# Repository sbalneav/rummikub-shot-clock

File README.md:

# Rummikub Shot Clock

A 60-second turn timer that fits inside one of those novelty "Easy" buttons. Press the button to end your turn: the next player's 60 seconds start. If time runs out, it beeps until somebody presses the button.

- **Project home:** https://github.com/sbalneav/rummikub-shot-clock
- **Illustrated overview:** https://claude.ai/artifact/5sadpqRUegUsPd4Guqu1sk (schematic, how it works and parts, in a page that's easy to read on a phone)

> **Status: rev A, not yet built or tested.** The schematic and PCB pass KiCad's design-rule check, but nobody has built a board yet. Breadboard it first, and please open an issue with what you find.

## How it works

| Stage | Part | What it does |
|---|---|---|
| Timer | U1 (555) | A one-shot. The Easy Button shorts the timing cap C1, which triggers the 555 and restarts the count. After about 1.1 × (R1 + VR1) × C1, the output goes low. Pin 7 is not used, so C1 keeps charging and the timer never retriggers itself. |
| Inverter | Q1 | Turns "timer finished" into ALARM high. |
| Tone | U2 (555) | An oscillator at about 1.5 kHz, held in reset until ALARM goes high. |
| Pulser (optional) | U3 (555) | About 2 Hz on/off, for a beep-beep-beep instead of a steady tone. Set it with JP1. |
| Driver | Q2 | Drives the button's 8 Ω speaker. |

What it does when used:

- **Every press restarts the full time**, whether you press during the countdown or during the beep. Contact bounce doesn't matter.
- **At power-on the countdown starts by itself.**

The optional pulser is shown here:

## Choosing a 555 and a battery

The board takes either type of 555. They have the same pinout and footprint, so the only difference is the power supply.

| Chips | Battery | R9 | Idle current | Notes |
|---|---|---|---|---|
| **TLC555 / LMC555 / ICM7555** (CMOS) | 2×AA or 2×AAA (3 V) | 10 Ω ¼ W | ~0.3 mA | Lowest drain. Uses the button's own 2-cell holder if it has one |
| **NE555** (bipolar) | 4×AA or 4×AAA (6 V) | 22 Ω ½ W | ~10–15 mA | The cheap 555s from bulk packs |
| **NE555** (bipolar) | 9 V battery | 47 Ω ½ W | ~10–15 mA | Fewer hours, but easy to fit |

- **An NE555 needs at least 4.5 V,** so it won't run from 2 cells. 3 cells (4.5 V) is marginal and quits as the batteries run down. Use 4 cells or a 9 V battery.
- **R9 sets the speaker current.** Raise it with the supply voltage as shown so it doesn't overheat.
- **Nothing else changes.** The turn length works the same at any supply voltage, so VR1 has the same range. The capacitors are rated 16 V.
- **Current while beeping** is about 150–200 mA with any option. Use the power switch between game nights, especially with NE555s.

## Ordering boards

Upload **`pcb/rummikub-shot-clock-gerbers.zip`** to any PCB fab (JLCPCB, PCBWay, OSH Park and so on).

| Setting | Value |
|---|---|
| Layers | 2 |
| Size | 72 × 58 mm |
| Thickness | 1.6 mm |
| Copper | 1 oz |
| Minimum track / space | 0.4 / 0.25 mm |
| Smallest drill | 0.45 mm (vias) |
| Parts | All through-hole |

The default settings at any fab will do.

| Front | Back |
|---|---|
|  |  |

**Check the size before you order.** Measure the inside of your Easy Button. The board is 72 × 58 mm and has two M3 mounting holes. If it doesn't fit, the layout scripts in `tools/` make it easy to change the outline and rebuild.

## Parts

See [`pcb/BOM.csv`](pcb/BOM.csv). For a steady tone only, leave out U3, R10, R11, C5, C7 and C10, and fit the JP1 jumper on pins 1-2.

## Building and setup

1. **Gut the button.** Cut or lift the traces from the original sound chip to the dome switch and the speaker. Wire those to J3 (BUTTON) and J4 (SPKR). Wire the battery to J1 and an on/off switch to J2. Choose the battery and R9 from the table under "Choosing a 555 and a battery".
2. **Check transistor pinouts.** The footprints are E-B-C, which matches the 2N3904, PN2222A and 2N4401. Some parts sold as 2N2222 are C-B-E.
3. **Set the time.** Use a stopwatch and adjust VR1 until the beep comes at 60 s, timing from when you release the button. Electrolytic caps vary by ±20%, so the formula only gets you close. Check again after a few hours powered, because new caps drift.
4. **Choose steady or pulsed.** JP1 on 1-2 gives a steady tone. On 2-3 it gives a pulsed beep.

## Repository layout

```
schematic/   schematic as PNG, SVG and PDF, plus the pulser add-on
pcb/         KiCad 9 board, Gerbers + drill (zipped), BOM, renders, DRC report
tools/       the Python scripts that generated the schematic and the board
```

The board was generated by script with the KiCad 9 `pcbnew` Python API and autorouted with [Freerouting](https://github.com/freerouting/freerouting). To rebuild it, run `tools/build_board.py`, export Specctra DSN, route it with Freerouting, then run `tools/finish_board.py`. You can also open `pcb/rummikub-shot-clock.kicad_pcb` in KiCad and edit it by hand. The DRC report lists one harmless warning: a small fragment of ground fill near C4, whose ground pin has its own trace.

## Credits and license

Designed by Scott Balneaves with Claude (Anthropic's AI model), which did the circuit design, schematic and PCB layout.

Hardware is licensed under the [CERN Open Hardware Licence v2 – Permissive](LICENSE).

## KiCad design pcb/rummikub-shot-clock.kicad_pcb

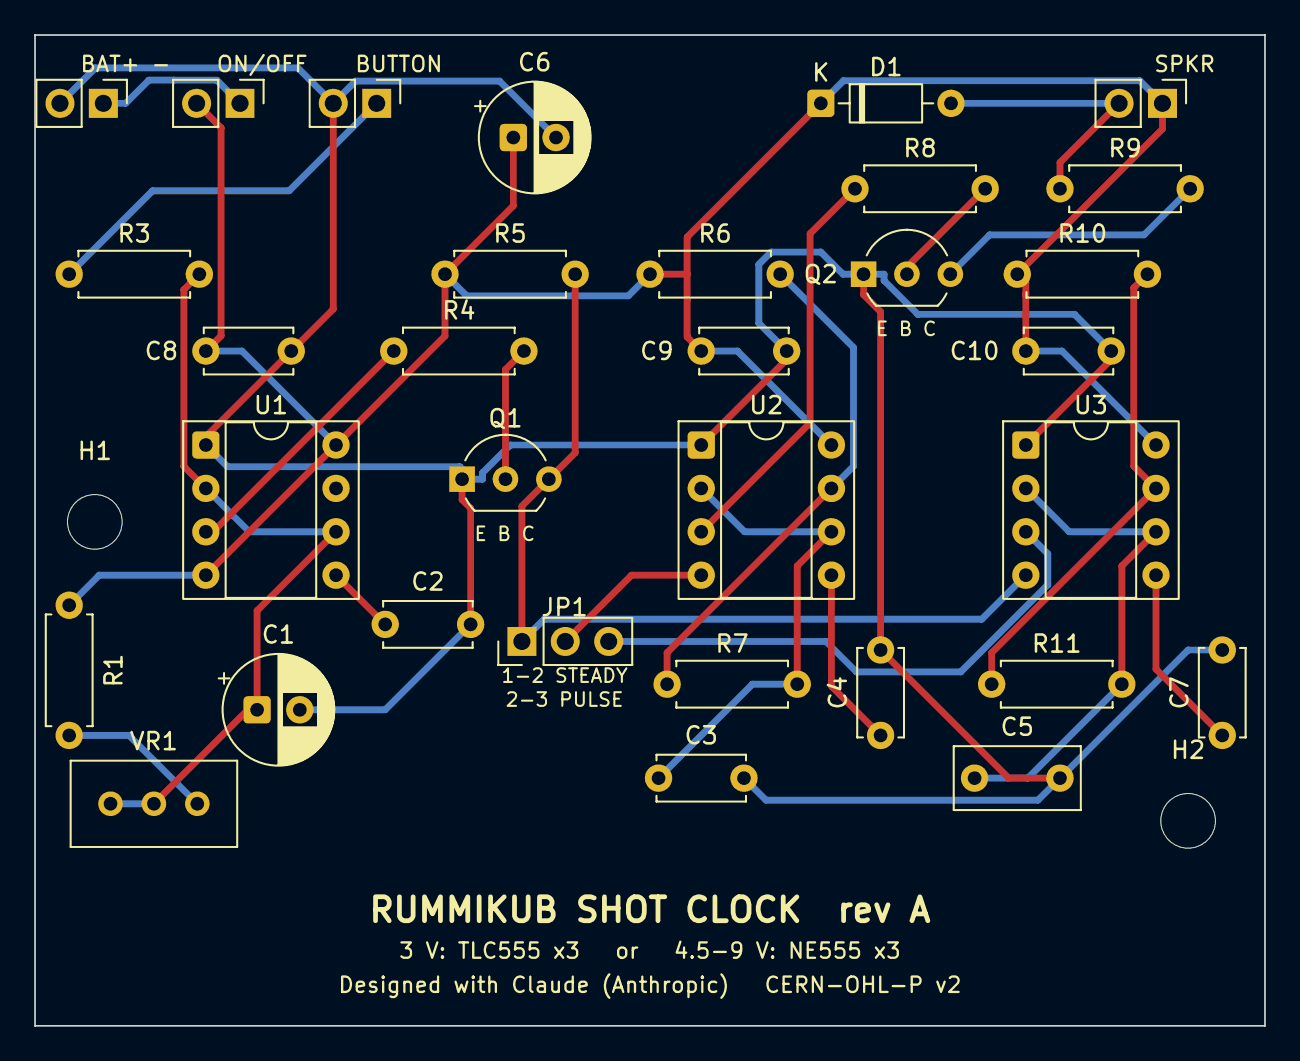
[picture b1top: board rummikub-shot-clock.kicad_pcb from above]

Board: 2 copper layers, 72.0 x 58.0 mm, 34 parts (0 on the bottom side), 22 nets.

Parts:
C1, C6: 220uF; CP_Radial_D6.3mm_P2.50mm
C2, C4, C7: 10nF; C_Disc_D5.0mm_W2.5mm_P5.00mm
C3: 47nF; C_Disc_D5.0mm_W2.5mm_P5.00mm
C5: 1uF film; C_Rect_L7.2mm_W3.5mm_P5.00mm_FKS2_FKP2_MKS2_MKP2
C8, C9, C10: 100nF; C_Disc_D5.0mm_W2.5mm_P5.00mm
D1: 1N4148; D_DO-35_SOD27_P7.62mm_Horizontal
H1, H2: M3; MountingHole_3.2mm_M3
J1: BATTERY; PinHeader_1x02_P2.54mm_Vertical
J2: POWER_SW; PinHeader_1x02_P2.54mm_Vertical
J3: EASY_BTN; PinHeader_1x02_P2.54mm_Vertical
J4: SPEAKER; PinHeader_1x02_P2.54mm_Vertical
JP1: STEADY/PULSE; PinHeader_1x03_P2.54mm_Vertical
Q1: 2N3904; TO-92_Inline_Wide
Q2: 2N2222A; TO-92_Inline_Wide
R1: 150k; R_Axial_DIN0207_L6.3mm_D2.5mm_P7.62mm_Horizontal
R3: 22R; R_Axial_DIN0207_L6.3mm_D2.5mm_P7.62mm_Horizontal
R4, R7, R10: 10k; R_Axial_DIN0207_L6.3mm_D2.5mm_P7.62mm_Horizontal
R5: 100k; R_Axial_DIN0207_L6.3mm_D2.5mm_P7.62mm_Horizontal
R6: 1k; R_Axial_DIN0207_L6.3mm_D2.5mm_P7.62mm_Horizontal
R8: 680R; R_Axial_DIN0207_L6.3mm_D2.5mm_P7.62mm_Horizontal
R9: 10R; R_Axial_DIN0207_L6.3mm_D2.5mm_P7.62mm_Horizontal
R11: 330k; R_Axial_DIN0207_L6.3mm_D2.5mm_P7.62mm_Horizontal
U1, U2, U3: TLC555; DIP-8_W7.62mm_Socket
VR1: 250k; Potentiometer_Bourns_3296W_Vertical

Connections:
+3V: C6.1, C8.1, C9.1, C10.1, D1.1, J2.2, J4.1, R1.2, R5.1, R6.1, R10.1, U1.4, U1.8, U2.8, U3.8
ALARM: JP1.1, Q1.3, R5.2, U3.4
B1: Q1.2, R4.2
B2: Q2.2, R8.2
BTN: J3.1, R3.1
CV1: C2.1, U1.5
CV2: C4.1, U2.5
CV3: C7.1, U3.5
DIS2: R6.2, R7.1, U2.7
DIS3: R10.2, R11.1, U3.7
GND: C1.2, C2.2, C3.2, C4.2, C5.2, C6.2, C7.2, C8.2, C9.2, C10.2, J1.2, J3.2, Q1.1, Q2.1, U1.1, U2.1, U3.1
OUT1: R4.1, U1.3
OUT2: R8.1, U2.3
PULSE: JP1.3, U3.3
RST2: JP1.2, U2.4
RT1: R1.1, VR1.1
SPK_C: Q2.3, R9.2
SPK_N: D1.2, J4.2, R9.1
TH2: C3.1, R7.2, U2.2, U2.6
TH3: C5.1, R11.2, U3.2, U3.6
TIMING: C1.1, R3.2, U1.2, U1.6, VR1.2, VR1.3
VBAT: J1.1, J2.1

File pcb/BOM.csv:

Ref,Qty,Value,Package / footprint,Notes
U1 U2 U3,3,TLC555 / LMC555 / ICM7555 (3 V) or NE555 (4.5-9 V),DIP-8,Pick the chip to suit the battery (see README). U3 only needed for pulsed beep
-,3,DIP-8 socket,DIP-8,Recommended
R1,1,150k,Axial 1/4 W (7.62 mm pitch),
VR1,1,250k multi-turn trimmer (Bourns 3296W-1-254),3296W,Sets turn length (about 36-97 s)
R3,1,22R,Axial 1/4 W,Protects the button contacts
R4,1,10k,Axial 1/4 W,
R5,1,100k,Axial 1/4 W,
R6,1,1k,Axial 1/4 W,
R7,1,10k,Axial 1/4 W,
R8,1,680R,Axial 1/4 W,
R9,1,10R 1/4 W @ 3 V | 22R 1/2 W @ 6 V | 47R 1/2 W @ 9 V,Axial,Speaker current limit: scale with supply voltage
R10,1,10k,Axial 1/4 W,Pulser only
R11,1,330k,Axial 1/4 W,Pulser only
C1,1,220uF 16 V+ electrolytic,Radial D6.3 mm P2.5 mm,Timing cap. Low-leakage type preferred
C6,1,220uF 16 V+ electrolytic,Radial D6.3 mm P2.5 mm,Supply bulk cap
C2 C4 C7,3,10nF ceramic,Disc P5.0 mm,C7 pulser only
C3,1,47nF ceramic or film,Disc P5.0 mm,Sets tone pitch (~1.5 kHz)
C5,1,1uF film,Box 7.2 x 3.5 mm P5.0 mm,Pulser only
C8 C9 C10,3,100nF ceramic,Disc P5.0 mm,Decoupling. C10 pulser only
Q1,1,2N3904,TO-92 (E-B-C),
Q2,1,PN2222A or 2N4401,TO-92 (E-B-C),Check pinout: some 2N2222 parts are C-B-E
D1,1,1N4148,DO-35,Cathode band toward the K mark
JP1,1,1x3 pin header + jumper,2.54 mm,1-2 steady tone / 2-3 pulsed
J1-J4,4,1x2 pin header or wire,2.54 mm,Battery / power switch / Easy Button switch / speaker
S1,1,SPST switch,off-board,Power
B1,1,2xAA/AAA (TLC555) or 4xAA/AAA or 9 V (NE555),off-board,See README power table
LS1,1,8 ohm speaker,off-board,Existing Easy Button speaker

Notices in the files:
pcb/rummikub-shot-clock.kicad_pcb:
Designed with Claude (Anthropic) CERN-OHL-P v2
